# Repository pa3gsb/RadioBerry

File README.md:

RadioBerry - Ham Radio cape for Raspberry PI
==============================================

## Main purpose of the project:

- Building a HAM Radio
- Learning (from noob to guru)

## Radioberry:

- Raspberry PI 2 Model B
- Radio extension board (cape)
	- using AD9866 (12 bit)  for RX and TX modes.

## Radioberry Configurations:

	Initialy i had the idea of using JAVA as then main programming language, 
	but the lack of speed when reading and writing to the GPIO of the raspberry pi 
	forced me to use the 'C' programming language.
	
	Setting the SI570 at the right fequency is done using the I2C bus of the pi and a JAVA progam.

	Three applications are being under development:
	
	- HermesLite 
	- Radio Berry
		On the RPI a webserver (using websockets for spectrum and audio) including the ported WDSP lib
	- Standalone transceiver

## HermesLite

Using a SDR program via the OPENHPSDR protocol and a network connection.

Starting hermes lite (c-program) using the following command:  sudo ./hermeslite

Start a SDR software program; 

## (Web) RadioBerry

Starting RadioBerry using the following command:  java -jar radioberry.jar 

Internally using the WDSP library.

Oeps.. in the WeServer class i hard coded an IP address ... for now modify and export the jar file...

Open a modern browser and start the URL ; i have created an initial ssb.html! 

For different modes an unique interface can be designed.

Because of the performance problems i have to change from JAVA using an embedded JETTY server to C using mongoose as webserver.
But the idea of making special pages for the different modes still stands!

## Standalone transceiver

Using a touch display and maybe some knobs.... 

As DSP lib using the WDSP library.

## Hardware

Schema and layout available. The print is created by elecrow. 

As can be seen in the picture the first components are mounted and the first firmware is loaded; showing the heart beat!

Some schema and layout errors:

	- )	Pin 23 AD9866 not connected to FPGA!
	- )	10 MHz not connected to 3.3V
	- ) LED for the 1V2 is not needed; the LED need at least 1.4..1.5V

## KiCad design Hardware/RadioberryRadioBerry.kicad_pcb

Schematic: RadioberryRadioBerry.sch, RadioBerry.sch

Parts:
C100, C101, C110, C111, C113, C114, C115, C116, C120, C121, C123, C124, C125, C126, C127, C128, C129, C130, C131, C132, C133, C134, C141, C144, C147, C148, C151, C160, C161, C163, C164, C165, C166, C167, C168, C169, C170, C200, C201, C202, C203, C204, C205, C206, C207, C208, C209, C211: 100n; RCL_C0603
C102, C112, C122, C162: 100uF; RCL_SMC_A
C140, C143, C146, C150, C301: 10n; RCL_C0603
C142, C145, C149, C152: 10uF; RCL_SMC_A
C210: 10uF; RCL_C1206
D1: PA3GSB_SOD-323
F200, F201, F202, F203: MURATA-FILTER_NFM21C
IC100, IC101: LD1117S33; V-REG_SOT223
IC102: LD1117S25; V-REG_SOT223
IC103: LD1117S12; V-REG_SOT223
IC200: AD9866; AD9866_CP_64_3
IC300: SI570; SILABS_8-PIN
IC301: 10MHz; AVS-CLOCK_MODEL625
IC400: EP3C25E144; ALTERA-CYCLONE-III_EQFP144
JP1: 2x20; PINHEAD_2X20
JP2: 2x10; PINHEAD_2X10
L1, L140, L141, L142, L143: FB; WUERTH-ELEKTRONIK_0805
LED1V2, LED2V5, LED3V3A805, LED3V3B805, LED801, LED802: RED; LED_CHIP-LED0805
LED803, LED804: GREEN; LED_CHIP-LED0805
R100: 120R; RCL_R0805
R101, R102, R800, R801, R802, R803: 2k2; RCL_R0805
R103, R104: 1K; RCL_R0805
R201: 1K6; RCL_R0805
R202, R203: 0; RCL_R0805
R301, R302: 4K7; RCL_R0805
R404, R405: 10K; RCL_R0805
T201, T202: BN-61-2402; PA3GSB_DIL06
X201, X202: BU-SMA-H; CON-COAX_BU-SMA-H

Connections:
/3V3A: C301.2, IC301.1 (ENABLE), IC301.4 (VDD)
/+1V2: C161.2, C162.+, C163.2, C164.2, C165.2, C166.2, C167.2, C168.2, C169.2, C170.2, IC103.4 (OUT), IC400.1 (VCC), IC400.5 (VCC), IC400.29 (VCC), IC400.34 (VCC), IC400.37 (VCC), IC400.38 (VCC), IC400.45 (VCC), IC400.61 (VCC), IC400.70 (VCC), IC400.73 (VCC), IC400.78 (VCC), IC400.84 (VCC), IC400.102 (VCC), IC400.109 (VCC), IC400.116 (VCC), IC400.124 (VCC), IC400.134 (VCC), IC400.138 (VCC), R100.2, R104.2
/+2V5: C111.2, C112.+, C113.2, C114.2, C115.2, C116.2, IC102.4 (OUT), IC400.3 (VCC), IC400.35 (VCC), IC400.75 (VCC), IC400.107 (VCC), R103.2
/+3V3: JP1.1, R203.2, R301.2, R302.2
/+3V3A: C121.2, C122.+, C123.2, C124.2, C125.2, C126.2, C127.2, C128.2, C129.2, C130.2, C131.2, C132.2, C133.2, C134.2, C160.2, IC101.4 (OUT), IC103.3 (IN), IC400.17 (VCC), IC400.26 (VCC), IC400.40 (VCC), IC400.47 (VCC), IC400.56 (VCC), IC400.62 (VCC), IC400.81 (VCC), IC400.93 (VCC), IC400.117 (VCC), IC400.122 (VCC), IC400.130 (VCC), IC400.139 (VCC), R101.2, R404.2, R405.2
/+3V3B: C101.2, C102.+, IC100.4 (OUT), L140.1, L141.1, L142.1, L143.1, R102.2
/+5V: C100.2, C110.2, C120.2, IC100.3 (IN), IC101.3 (IN), IC102.3 (IN), JP1.2, JP1.4, JP2.1, JP2.2, R202.2
/AVDD_ADC: C140.2, C141.2, C142.+, IC200.35 (AVDD), IC200.40 (AVDD_2), L140.2
/AVDD_DAC: C143.2, C144.2, C145.+, IC200.43 (AVDD_3), L141.2
/CLK: IC200.57 (OSCIN), IC300.4 (CLK+)
/CLKVDD: C146.2, C147.2, C148.2, C149.+, IC200.58 (CLKVDD), IC300.6 (VDD), L142.2
/DEBUG_1: IC400.30 (IO30), R800.2
/DEBUG_2: IC400.28 (IO28), R801.2
/DEBUG_3: IC400.4 (IO4), R802.2
/DEBUG_4: IC400.6 (IO6), R803.2
/DVDD: C150.2, C151.2, C152.+, IC200.17 (DRVDD), IC200.60 (DVDD), IC200.64 (DRVDD_2), L143.2
/FPGA_ADIO00: IC200.12 (ADIO0/RX0), IC400.83 (IO83)
/FPGA_ADIO01: IC200.11 (ADIO1/RX1), IC400.85 (IO85)
/FPGA_ADIO02: IC200.10 (ADIO2/RX2), IC400.86 (IO86)
/FPGA_ADIO03: IC200.9 (ADIO3/RX3), IC400.87 (IO87)
/FPGA_ADIO04: IC200.8 (ADIO4/RX4), IC400.98 (IO98)
/FPGA_ADIO05: IC200.7 (ADIO5/RX5), IC400.99 (IO99)
/FPGA_ADIO06: IC200.6 (ADIO6/TX0), IC400.100 (IO100)
/FPGA_ADIO07: IC200.5 (ADIO7/TX1), IC400.101 (IO101)
/FPGA_ADIO08: IC200.4 (ADIO8/TX2), IC400.103 (IO103)
/FPGA_ADIO09: IC200.3 (ADIO9/TX3), IC400.104 (IO104)
/FPGA_ADIO10: IC200.2 (ADIO10/TX4), IC400.105 (IO105)
/FPGA_ADIO11: IC200.1 (ADIO11/TX5), IC400.106 (IO106)
/FPGA_CE0: IC400.137 (IO137)
/FPGA_CE0_SPI0: IC400.43 (IO43), JP1.24
/FPGA_CE0_SPI1: IC400.50 (IO50), JP1.12
/FPGA_CE1_SPI0: IC400.42 (IO42), JP1.26
/FPGA_CE1_SPI1: IC400.51 (IO51), JP1.11
/FPGA_CE2_SPI1: IC400.33 (IO33), JP1.36
/FPGA_CLKOUT: IC200.19 (CLKOUT1), IC400.72 (IO72)
/FPGA_CLOCK: IC301.3 (CLK), IC400.25 (CLK3)
/FPGA_CONF_DONE: IC400.92 (CONF_DONE), JP1.15, R404.1
/FPGA_DATA[0]: IC400.13 (IO13), JP1.33
/FPGA_DCLK: IC400.12 (DCLK), JP1.18
/FPGA_MISO_SPI0: IC400.46 (IO46), JP1.21
/FPGA_MISO_SPI1: IC400.39 (IO39), JP1.35
/FPGA_MODE: IC200.53 (MODE), IC400.110 (IO110)
/FPGA_MOSI_SPI0: IC400.49 (IO49), JP1.19
/FPGA_MOSI_SPI1: IC400.32 (IO32), JP1.38
/FPGA_NCONFIG: IC400.14 (NCONFIG), JP1.13
/FPGA_NSTATUS: IC400.9 (NSTATUS), JP1.37, R405.1
/FPGA_PGA0: IC200.29 (PGA0), IC400.59 (IO59)
/FPGA_PGA1: IC200.28 (PGA1), IC400.60 (IO60)
/FPGA_PGA2: IC200.27 (PGA2), IC400.64 (IO64)
/FPGA_PGA3: IC200.26 (PGA3), IC400.65 (IO65)
/FPGA_PGA4: IC200.25 (PGA4), IC400.66 (IO66)
/FPGA_PGA5: IC200.24 (GAIN/PGA5), IC400.67 (IO67)
/FPGA_RESET: IC200.30 (RESET), IC400.58 (IO58)
/FPGA_RXCLK: IC200.16 (RXCLK), IC400.76 (IO76)
/FPGA_RXEN: IC200.13 (RXEN/RXSYNC), IC400.80 (IO80)
/FPGA_SCLK: IC200.22 (SCLK), IC400.68 (IO68)
/FPGA_SCLK_SPI0: IC400.44 (IO44), JP1.23
/FPGA_SCLK_SPI1: IC400.31 (IO31), JP1.40
/FPGA_SDIO: IC200.20 (SDIO), IC400.71 (IO71)
/FPGA_SDO: IC200.21 (SDO), IC400.69 (IO69)
/FPGA_TXCLK: IC200.15 (TXCLK/TXQUIET), IC400.77 (IO77)
/FPGA_TXEN: IC200.14 (TXEN/TXSYNC), IC400.79 (IO79)
/IO-01: IC400.144 (IO144), JP2.3
/IO-02: IC400.143 (IO143), JP2.4
/IO-03: IC400.142 (IO142), JP2.5
/IO-04: IC400.141 (IO141), JP2.6
/IO-05: IC400.136 (IO136), JP2.7
/IO-06: IC400.135 (IO135), JP2.8
/IO-07: IC400.133 (IO133), JP2.9
/IO-08: IC400.132 (IO132), JP2.10
/IO-09: IC400.125 (IO125), JP2.11
/IO-10: IC400.121 (IO121), JP2.12
/IO-11: IC400.120 (IO120), JP2.13
/IO-12: IC400.119 (IO119), JP2.14
/IO-13: IC400.115 (IO115), JP2.15
/IO-14: IC400.114 (IO114), JP2.16
/IO-15: IC400.113 (IO113), JP2.17
/IO-16: IC400.112 (IO112), JP2.18
/N$1: L1.2, R202.1, R203.1
/N$2: F203.3, T202.1 (P2)
/N$3: C205.2, T202.4 (S1)
/N$4: C201.2, L1.1, T201.5 (ST)
/N$5: C202.1, C203.2, D1.A
/N$6: IC200.50 (IOUT_N+), T201.4 (S1)
/N$7: IC200.46 (IOUT_N-), T201.6 (S2)
/N$8: C206.2, T202.6 (S2)
/N$10: LED3V3B805.A, R102.1
/N$11: LED2V5.A, R103.1
/N$13: C206.1, IC200.37 (RX-)
/N$14: C204.2, T202.5 (ST)
/N$15: C205.1, IC200.38 (RX+)
/N$16: LED801.A, R800.1
/N$17: LED802.A, R801.1
/N$18: LED803.A, R802.1
/N$19: LED804.A, R803.1
/N$20: LED3V3A805.A, R101.1
/N$23: LED1V2.A, R104.1
/N$25: F202.3, F203.1
/N$28: C202.2, X202.1
/N$29: C203.1, F202.1
/N$30: C207.2, C209.2, C210.2, IC200.33 (REFT)
/N$32: C208.2, C209.1, C210.1, IC200.32 (REFB)
/N$33: C211.2, IC200.42 (REFIO)
/N$34: IC200.41 (REFADJ), R201.1
/N$69: C200.2, X201.1
/N$71: C200.1, F200.1
/N$72: F200.3, F201.1
/N$73: F201.3, T201.3 (P1)
/SCL: IC300.8 (SCL), JP1.5, R301.1
/SDA: IC300.7 (SDA), JP1.3, R302.1
/SI570_OE: IC300.2 (OE), IC400.111 (IO111)
GND: C100.1, C101.1, C102.-, C110.1, C111.1, C112.-, C113.1, C114.1, C115.1, C116.1, C120.1, C121.1, C122.-, C123.1, C124.1, C125.1, C126.1, C127.1, C128.1, C129.1, C130.1, C131.1, C132.1, C133.1, C134.1, C140.1, C141.1, C142.-, C143.1, C144.1, C145.-, C146.1, C147.1, C148.1, C149.-, C150.1, C151.1, C152.-, C160.1, C161.1, C162.-, C163.1, C164.1, C165.1, C166.1, C167.1, C168.1, C169.1, C170.1, C201.1, C204.1, C207.1, C208.1, C211.1, C301.1, D1.B, F200.2@1 (2), F200.2@2 (2), F201.2@1 (2), F201.2@2 (2), F202.2@1 (2), F202.2@2 (2), F203.2@1 (2), F203.2@2 (2), IC100.1 (ADJ), IC101.1 (ADJ), IC102.1 (ADJ), IC103.1 (ADJ), IC200.18 (DRVSS), IC200.31 (AVSS), IC200.34 (AVSS_2), IC200.36 (AVSS_3), IC200.39 (AVSS_4), IC200.44 (AVSS_5), IC200.47 (AVSS_6), IC200.48 (AVSS_7), IC200.54 (CONFIG), IC200.55 (CLKVSS), IC200.59 (DVSS), IC200.62 (PWR_DWN), IC200.63 (DRVSS_2), IC200.65 (EP), IC300.3 (GND), IC301.2 (GND), IC400.2 (GND), IC400.19 (GND), IC400.21 (NCE), IC400.27 (GND), IC400.36 (GND), IC400.41 (GND), IC400.48 (GND), IC400.57 (GND), IC400.63 (GND), IC400.74 (GND), IC400.82 (GND), IC400.94 (MSEL0), IC400.95 (GND), IC400.96 (MSEL1), IC400.97 (MSEL2), IC400.108 (GND), IC400.118 (GND), IC400.123 (GND), IC400.131 (GND), IC400.140 (GND), IC400.E (GND), JP1.6, JP1.9, JP1.14, JP1.20, JP1.25, JP1.30, JP1.34, JP1.39, JP2.19, JP2.20, LED1V2.C, LED2V5.C, LED3V3A805.C, LED3V3B805.C, LED801.C, LED802.C, LED803.C, LED804.C, R100.1, R201.2, T201.1 (P2), T202.3 (P1), X201.2, X201.3 (2), X201.4 (2), X201.5 (2), X202.2, X202.3 (2), X202.4 (2), X202.5 (2)

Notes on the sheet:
Power Supply
[100]
Configuration
1:1
8:1
Place only one
50 MHz LPF NFL21SP506X1C3

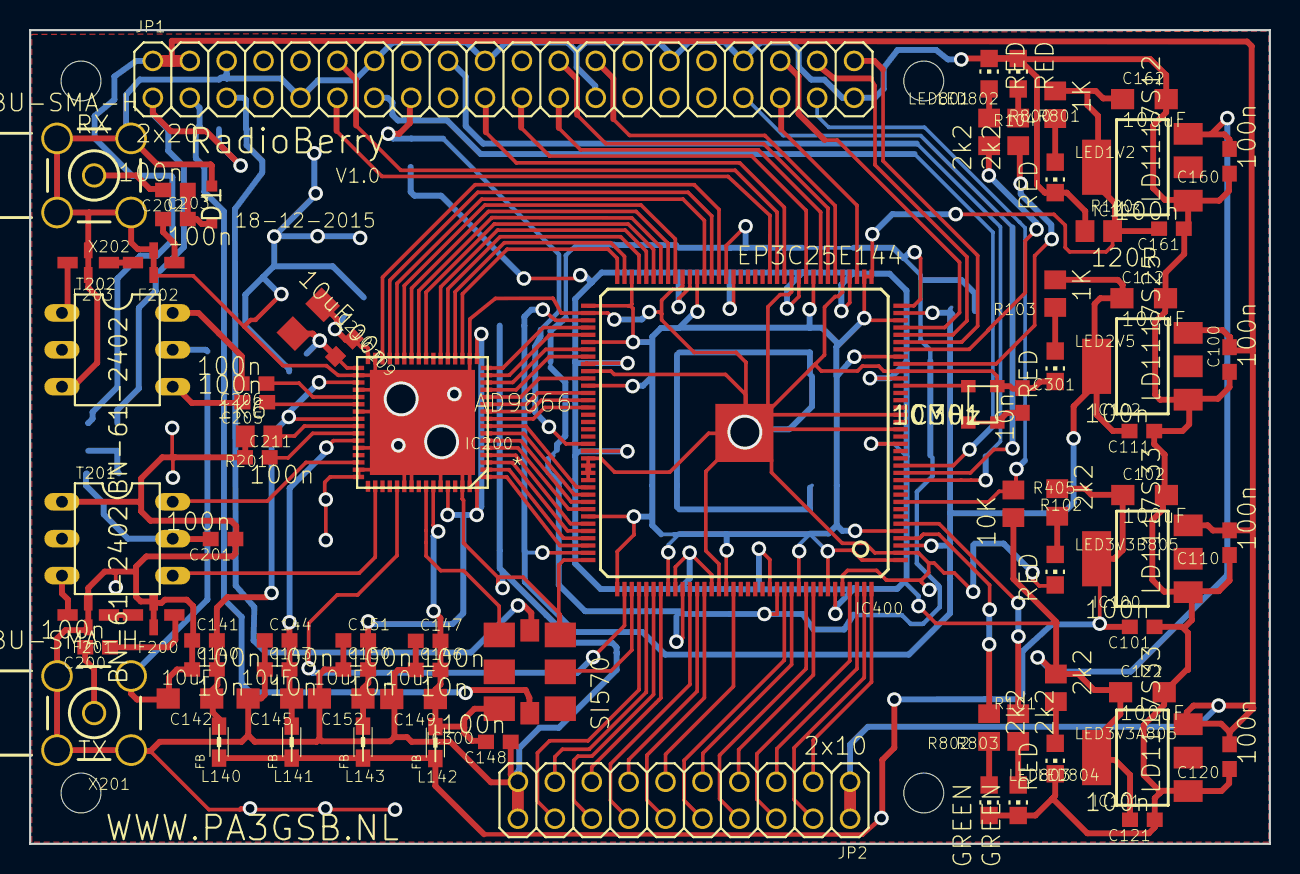
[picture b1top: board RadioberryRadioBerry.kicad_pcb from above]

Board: 2 copper layers, 85.3 x 56.0 mm, 114 parts (0 on the bottom side), 111 nets.

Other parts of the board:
@HOLE0, @HOLE1, @HOLE2, @HOLE3: (no value)

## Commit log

2015-09-27 change of plans
2015-09-27 test
2015-10-13 initial
2015-11-14 pcb v0.91
2015-12-18 radioberry pcb v1.0
2016-01-22 loading fpga added
2016-01-22 readme update
2016-01-30 radio operating in testmode
2016-02-01 powersdr running
2016-02-20 hpsdsr-protocol in 'c' performance problem solved
2016-03-16 ad9866 added
2016-04-21 transmit mode active
2016-05-17 sample rate and noise floor measurement
2016-05-17 clean
2016-05-20 noise floor; output file
2016-05-23 use of gnuplot
2016-05-23 screenprint
2016-06-04 project page
2016-06-04 project info
2016-06-11 undo change
2016-07-02 local audio added using simple pulseaudio library
2016-07-02 added standalone
2016-09-29 firmware improvement + using 3D Sound dongle mic and audio
2016-11-02 frontend + backend + si570 loader
2016-11-03 Att handling changed and the identification set to hermeslite
2016-11-05 side band reverted
2016-11-05 ptt out + side band reverted in firmware; 48K en 96K transmit for hermeslite solved
2016-11-12 new widgets + some work backend
2016-11-28 loading firmware using java + backend running incl wdsp en set freq
2016-11-28 backend and frontend without styling (next step websockets)
2016-12-13 spectrum and websocket server side
2016-12-22 spectrum data visible using websocket
2016-12-31 some small mods
2016-12-31 firmwareloader.jar included
2017-02-05 filter
2017-02-05 set an offset to freq 73728000
2017-02-25 2-receivers
2017-02-27 2 receivers useable for psdr but also spark sdr
2017-02-27 standalone now forked from pihpsdr
2017-03-04 2rx and tx
2017-03-11 rbf in juiste folder
2017-04-27 quisk tx problem solved
2017-05-25 masterclock en sdc timing
2017-05-25 gitignore
2017-05-31 firmwareloader 76.8
2017-06-05 before clean
2017-06-23 eagle project converted to kicad
2017-06-28 v1.1 PCB
2017-07-29 revert start frequency
2017-07-29 latest firmware
2017-08-03 programming si570 uses now the installed device params iso pa3gsb si570 parms
2017-08-12 timing and smaller fifo buffer
2017-08-12 time closure
2017-08-14 using small fifo and timing
2017-08-18 build
2017-08-26 multichannel added
2017-09-11 wspr
2017-09-12 remove tmp files
2017-09-12 removed tmp files
2017-10-21 update pi4j libs
2017-11-12 cw iambic; fixed settings
2017-11-13 pass key data to rpi
2017-11-18 cw-mode
2017-11-18 cw-doc
2017-12-04 pull ups added for cw dot and dash keys
2018-05-13 rb2 updates applied to rb1
